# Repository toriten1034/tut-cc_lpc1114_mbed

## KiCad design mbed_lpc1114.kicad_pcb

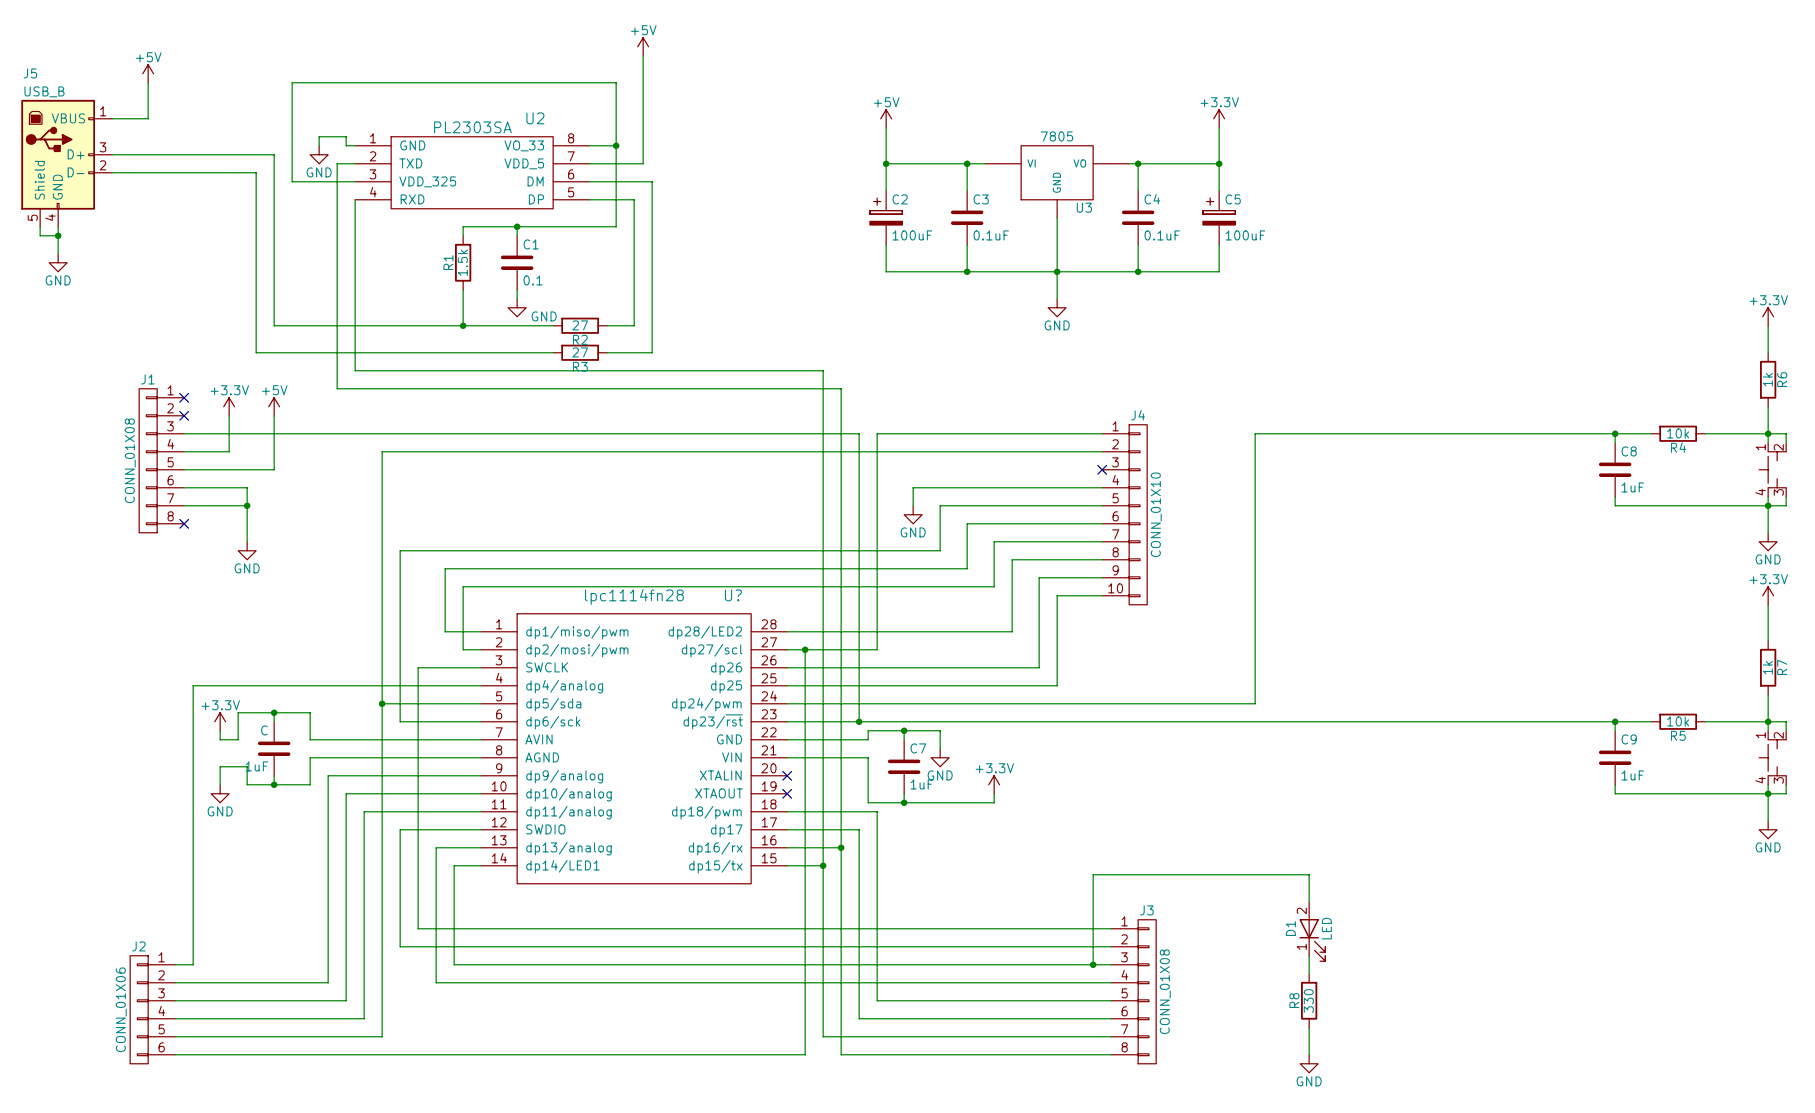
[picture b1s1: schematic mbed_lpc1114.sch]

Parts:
1uF: C; 10uF
C1: 0.1
C2, C5: 100uF
C3, C4: 0.1uF
C7, C8, C9: 1uF
D1: LED
J1, J3: CONN_01X08
J2: CONN_01X06
J4: CONN_01X10
J5: USB_B
R1: 1.5k
R2, R3: 27
R4, R5: 10k
R6, R7: 1k
R8: 330
U2: PL2303SA
U3: 7805
U4, U5: PushSwitch

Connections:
+3V3: 1uF.2, C4.1, C5.1, C7.2, J1.4, R6.1, R7.1, U3.VO; also elsewhere on the board
+5V: C2.1, C3.1, J1.5, J5.1 (VBUS), U2.7 (VDD_5), U3.VI
GND: 1uF.1, C1.2, C2.2, C3.2, C4.2, C5.2, C7.1, C8.2, C9.2, J1.6, J1.7, J4.4, J5.4 (GND), J5.5 (Shield), R8.1, U2.1 (GND), U3.GND, U4.3, U4.4, U5.3, U5.4; also elsewhere on the board
unnamed: C1.1, R1.2, U2.3 (VDD_325), U2.8 (VO_33)
unnamed 4: C8.1, R4.2; also elsewhere on the board
unnamed 5: C9.1, J1.3, R5.2; also elsewhere on the board
unnamed: D1.1 (K), R8.2
unnamed 7: D1.2 (A), J3.3; also elsewhere on the board
unnamed 8: J2.1; also elsewhere on the board
unnamed 9: J2.2; also elsewhere on the board
unnamed 10: J2.3; also elsewhere on the board
unnamed 11: J2.4; also elsewhere on the board
unnamed 12: J2.5, J4.2; also elsewhere on the board
unnamed 13: J2.6, J4.1; also elsewhere on the board
unnamed 14: J3.1; also elsewhere on the board
unnamed 15: J3.2; also elsewhere on the board
unnamed 16: J3.4; also elsewhere on the board
unnamed 17: J3.5; also elsewhere on the board
unnamed 18: J3.6; also elsewhere on the board
unnamed 19: J3.7, U2.4 (RXD); also elsewhere on the board
unnamed 20: J3.8, U2.2 (TXD); also elsewhere on the board
unnamed 21: J4.5; also elsewhere on the board
unnamed 22: J4.6; also elsewhere on the board
unnamed 23: J4.7; also elsewhere on the board
unnamed 24: J4.8; also elsewhere on the board
unnamed 25: J4.9; also elsewhere on the board
unnamed 26: J4.10; also elsewhere on the board
unnamed: J5.2 (D-), R3.2
unnamed: J5.3 (D+), R1.1, R2.2
unnamed: R2.1, U2.5 (DP)
unnamed: R3.1, U2.6 (DM)
unnamed: R4.1, R6.2, U4.1, U4.2
unnamed: R5.1, R7.2, U5.1, U5.2

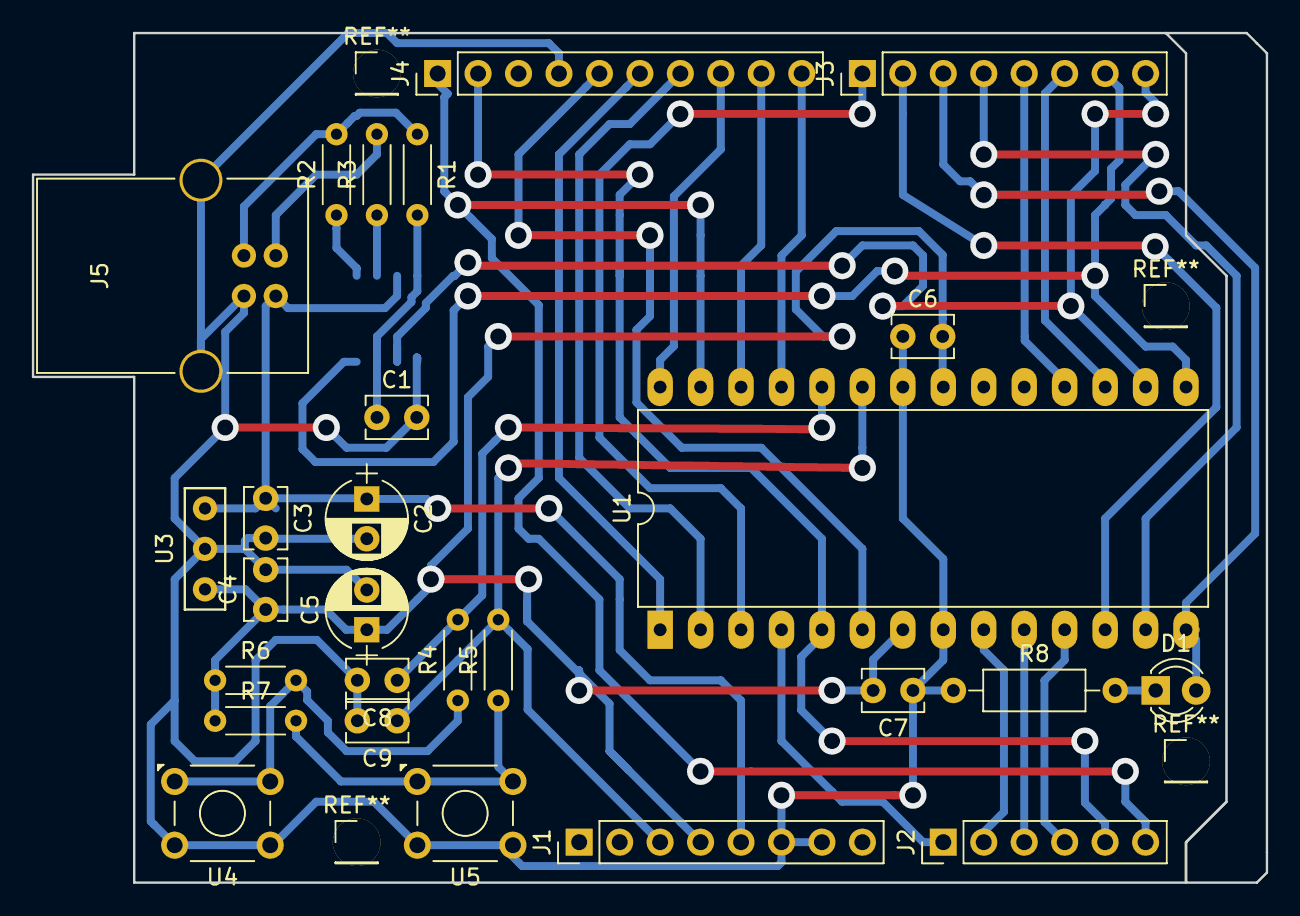
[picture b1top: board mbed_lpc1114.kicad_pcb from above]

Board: 2 copper layers, 77.5 x 53.3 mm, 28 parts (1 on the bottom side), 33 nets.

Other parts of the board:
C6: 1uF; C_Disc_D3.8mm_W2.6mm_P2.50mm
U1: lpc1114fn28; DIP-28_W15.24mm_LongPads

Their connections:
+3V3: C6.2, U1.7, U1.21; also elsewhere on the board
GND: C6.1, U1.8, U1.22; also elsewhere on the board
unnamed 4: U1.24; also elsewhere on the board
unnamed 5: U1.23; also elsewhere on the board
unnamed 7: U1.14; also elsewhere on the board
unnamed 8: U1.4; also elsewhere on the board
unnamed 9: U1.9; also elsewhere on the board
unnamed 10: U1.10; also elsewhere on the board
unnamed 11: U1.11; also elsewhere on the board
unnamed 12: U1.5; also elsewhere on the board
unnamed 13: U1.27; also elsewhere on the board
unnamed 14: U1.3; also elsewhere on the board
unnamed 15: U1.12; also elsewhere on the board
unnamed 16: U1.13; also elsewhere on the board
unnamed 17: U1.18; also elsewhere on the board
unnamed 18: U1.17; also elsewhere on the board
unnamed 19: U1.15; also elsewhere on the board
unnamed 20: U1.16; also elsewhere on the board
unnamed 21: U1.6; also elsewhere on the board
unnamed 22: U1.1; also elsewhere on the board
unnamed 23: U1.2; also elsewhere on the board
unnamed 24: U1.28; also elsewhere on the board
unnamed 25: U1.26; also elsewhere on the board
unnamed 26: U1.25; also elsewhere on the board

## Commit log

2017-04-29 ver1
2017-04-29 value
2017-04-29 パラメータ調整
2017-04-29 リセットピン修正
2017-04-29 ライブラリ修正
2017-04-30 ピン配置を修正
2017-04-30 ひとまず完成．LPCマイコンを動かしたい
2017-05-01 ベタグラウンドを追加
2017-05-01 ちょっと修正
